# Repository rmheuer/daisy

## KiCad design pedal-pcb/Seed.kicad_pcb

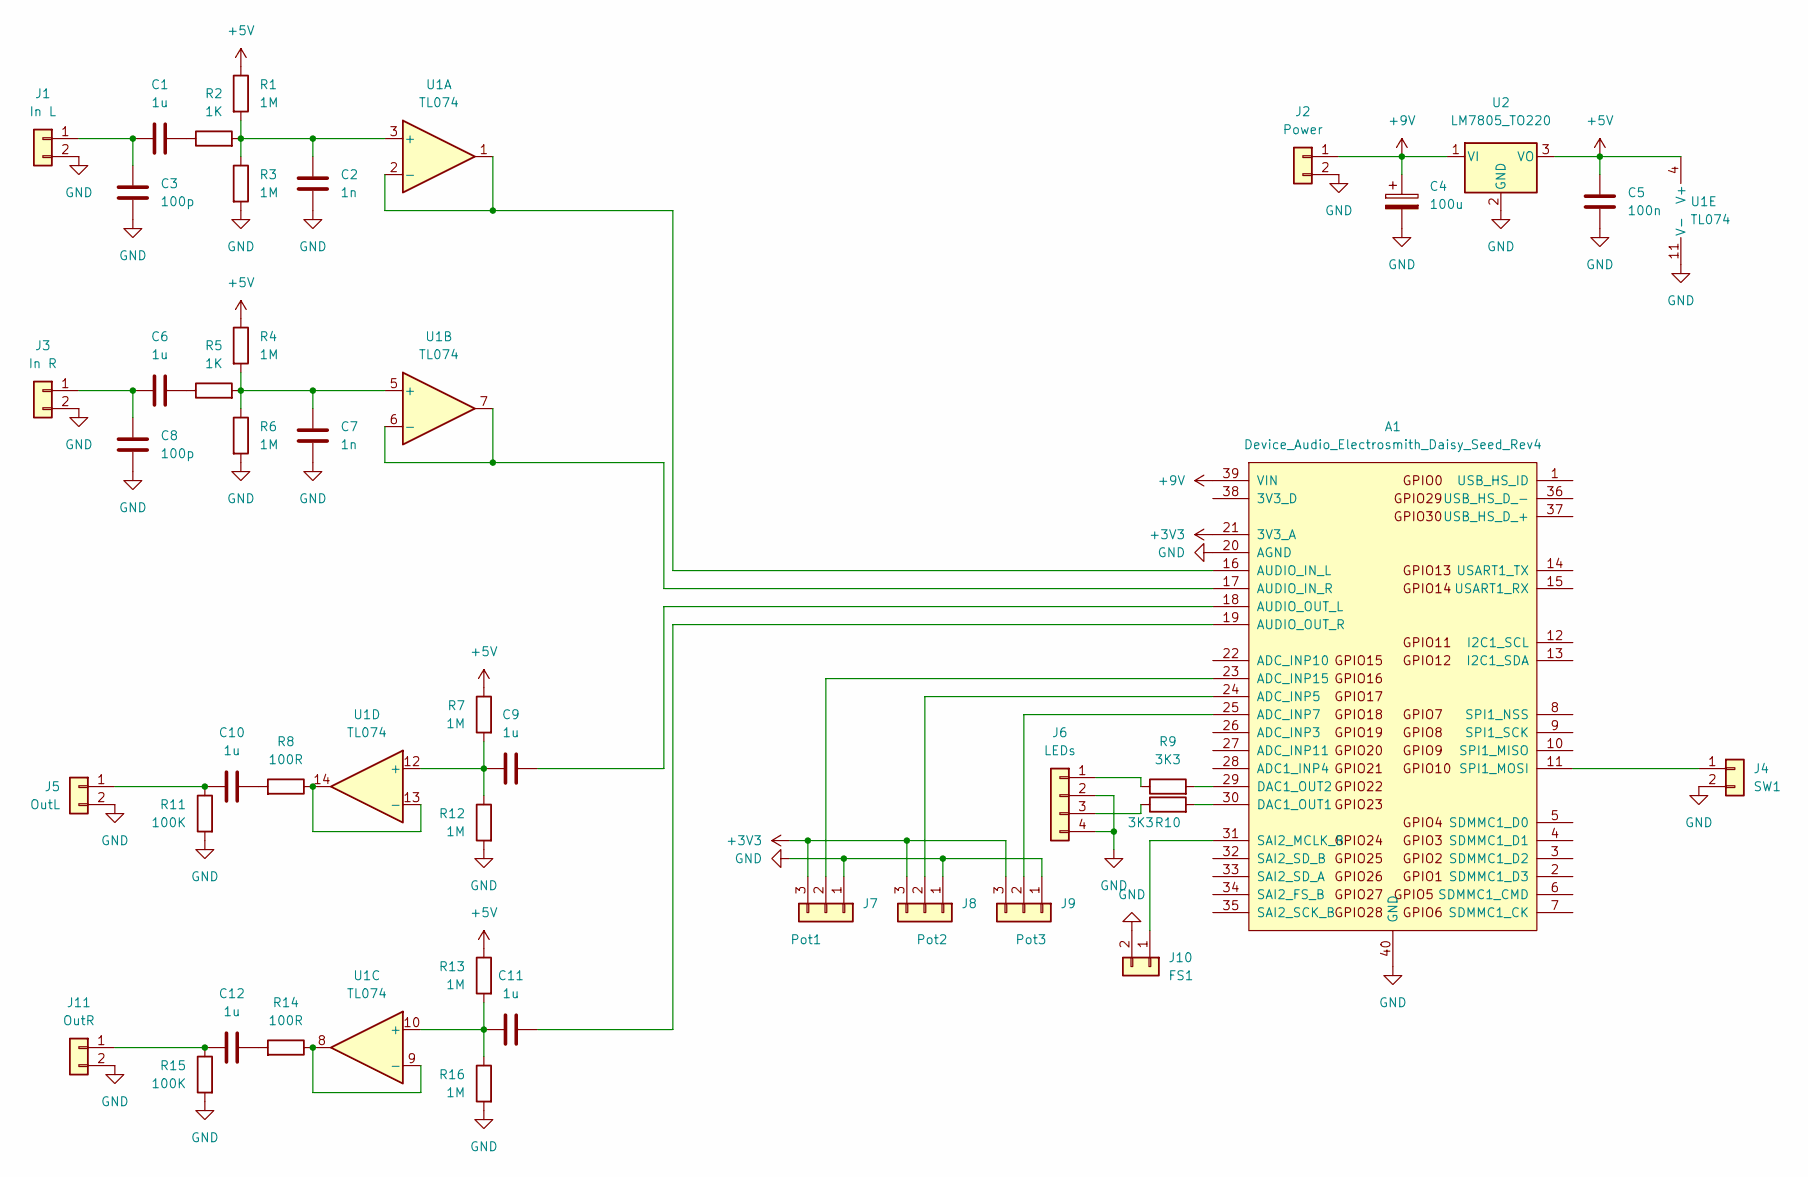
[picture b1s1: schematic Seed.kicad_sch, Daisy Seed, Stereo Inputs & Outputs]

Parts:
A1: Device_Audio_Electrosmith_Daisy_Seed_Rev4; Device_Audio_Electrosmith_Daisy_Seed
C1, C6, C9, C10, C11, C12: 1u; C_Rect_L7.0mm_W2.5mm_P5.00mm
C2, C7: 1n; C_Rect_L7.0mm_W2.5mm_P5.00mm
C3, C8: 100p; C_Rect_L7.0mm_W2.5mm_P5.00mm
C4: 100u; CP_Radial_D5.0mm_P2.00mm
C5: 100n; C_Rect_L7.0mm_W2.5mm_P5.00mm
J1: In L; PinSocket_1x02_P2.54mm_Vertical
J2: Power; PinSocket_1x02_P2.54mm_Vertical
J3: In R; PinSocket_1x02_P2.54mm_Vertical
J4: SW1; PinSocket_1x02_P2.54mm_Vertical
J5: OutL; PinSocket_1x02_P2.54mm_Vertical
J6: LEDs; PinSocket_1x04_P2.54mm_Vertical
J7: Pot1; PinSocket_1x03_P2.54mm_Vertical
J8: Pot2; PinSocket_1x03_P2.54mm_Vertical
J9: Pot3; PinSocket_1x03_P2.54mm_Vertical
J10: FS1; PinSocket_1x02_P2.54mm_Vertical
J11: OutR; PinSocket_1x02_P2.54mm_Vertical
R1, R3, R4, R6, R7, R12, R13, R16: 1M; R_Axial_DIN0207_L6.3mm_D2.5mm_P7.62mm_Horizontal
R2, R5: 1K; R_Axial_DIN0207_L6.3mm_D2.5mm_P7.62mm_Horizontal
R8, R14: 100R; R_Axial_DIN0207_L6.3mm_D2.5mm_P7.62mm_Horizontal
R9, R10: 3K3; R_Axial_DIN0207_L6.3mm_D2.5mm_P7.62mm_Horizontal
R11, R15: 100K; R_Axial_DIN0207_L6.3mm_D2.5mm_P7.62mm_Horizontal
U1: TL074; DIP-14_W7.62mm_Socket
U2: LM7805_TO220; TO-220-3_Vertical

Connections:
+3V3: A1.21 (3V3_A), J7.3, J8.3, J9.3
+5V: C5.1, R1.1, R4.1, R7.1, R13.1, U1.4 (V+), U2.3 (VO)
+9V: A1.39 (VIN), C4.1, J2.1, U2.1 (VI)
GND: A1.20 (AGND), A1.40 (GND), C2.2, C3.2, C4.2, C5.2, C7.2, C8.2, J1.2, J2.2, J3.2, J4.2, J5.2, J6.2, J6.4, J7.1, J8.1, J9.1, J10.2, J11.2, R3.2, R6.2, R11.2, R12.2, R15.2, R16.2, U1.11 (V-), U2.2 (GND)
unnamed: A1.11 (SPI1_MOSI), J4.1
unnamed: A1.16 (AUDIO_IN_L), U1.1, U1.2 (-)
unnamed: A1.17 (AUDIO_IN_R), U1.6 (-), U1.7
unnamed: A1.18 (AUDIO_OUT_L), C9.1
unnamed: A1.19 (AUDIO_OUT_R), C11.1
unnamed: A1.23 (ADC_INP15), J7.2
unnamed: A1.24 (ADC_INP5), J8.2
unnamed: A1.25 (ADC_INP7), J9.2
unnamed: A1.29 (DAC1_OUT2), R9.2
unnamed: A1.30 (DAC1_OUT1), R10.2
unnamed: A1.31 (SAI2_MCLK_B), J10.1
unnamed: C1.1, R2.1
unnamed: C1.2, C3.1, J1.1
unnamed: C2.1, R1.2, R2.2, R3.1, U1.3 (+)
unnamed: C6.1, R5.1
unnamed: C6.2, C8.1, J3.1
unnamed: C7.1, R4.2, R5.2, R6.1, U1.5 (+)
unnamed: C9.2, R7.2, R12.1, U1.12 (+)
unnamed: C10.1, R8.2
unnamed: C10.2, J5.1, R11.1
unnamed: C11.2, R13.2, R16.1, U1.10 (+)
unnamed: C12.1, R14.2
unnamed: C12.2, J11.1, R15.1
unnamed: J6.1, R9.1
unnamed: J6.3, R10.1
unnamed: R8.1, U1.13 (-), U1.14
unnamed: R14.1, U1.8, U1.9 (-)

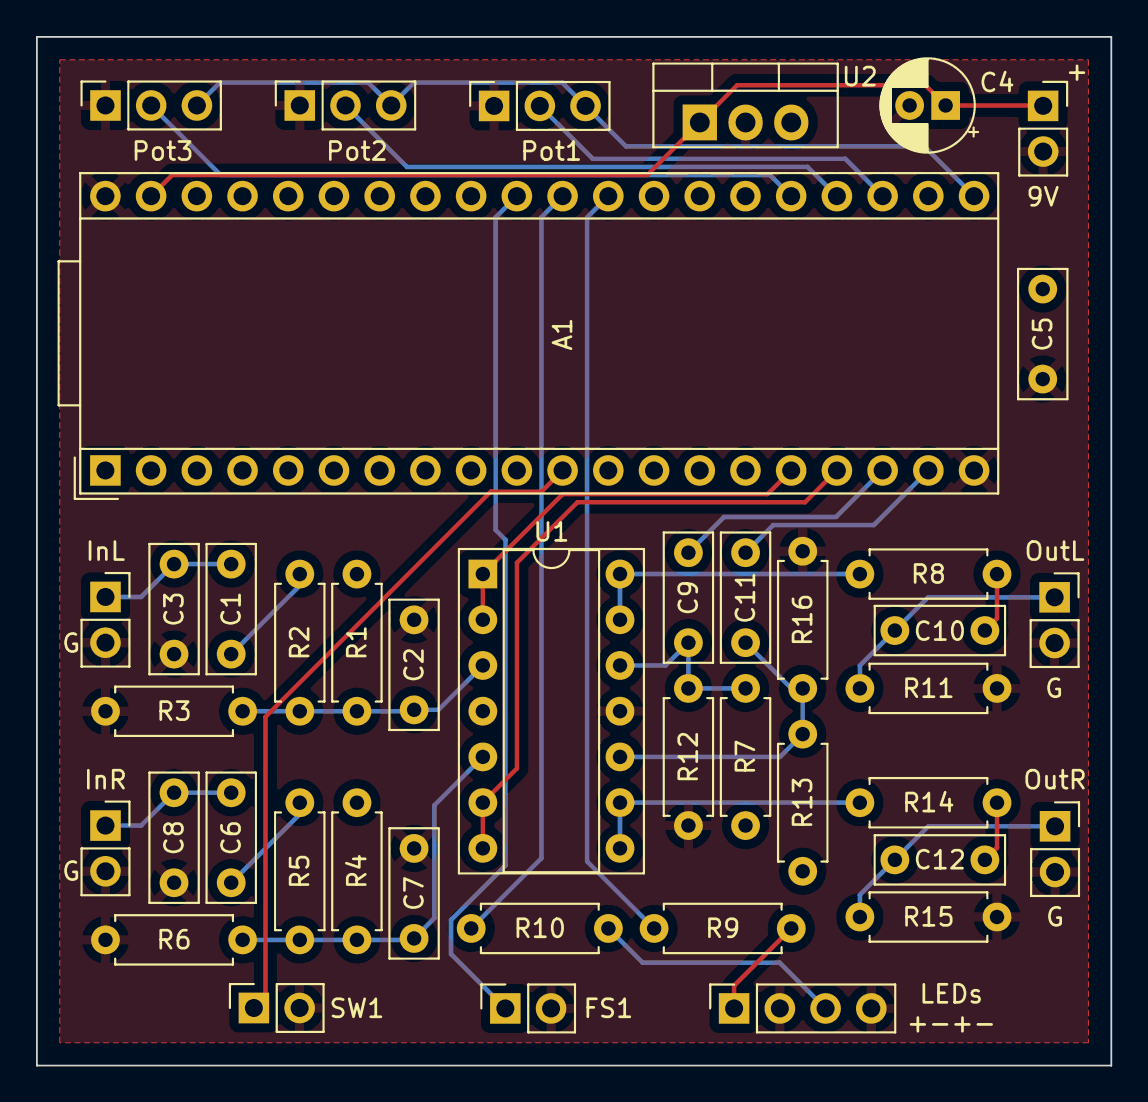
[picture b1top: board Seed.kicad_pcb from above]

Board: 2 copper layers, 59.7 x 57.1 mm, 42 parts (0 on the bottom side), 31 nets.

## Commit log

2024-03-18 add Patch.init() arduino examples
2024-03-18 apply GPL version 3.0 license
2024-03-18 fix line endings
2024-03-18 add cv examples
2024-03-18 cv output is 0v to 5v, needs validation
2024-03-18 cv output is 0v to 5v, missed knobs
2024-03-20 add patch-init doom and init eurorack-block examples
2024-03-20 add doom license note
2024-03-20 add header and doom example
2024-03-20 toggle switch unipolar/bipolar
2024-06-09 add pedal pcb
2024-06-09 Update PCB to KiCad 8
